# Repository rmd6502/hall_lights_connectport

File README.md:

# Hall Lights
## Directory
* TBXML
    An external library I use to parse XML
* color_picker
    An iOS front end
* hall_lights
    The Arduino sketch
* hardware
    Eagle CAD files
* lights
    Python source for the ConnectPort X2 to implement the server

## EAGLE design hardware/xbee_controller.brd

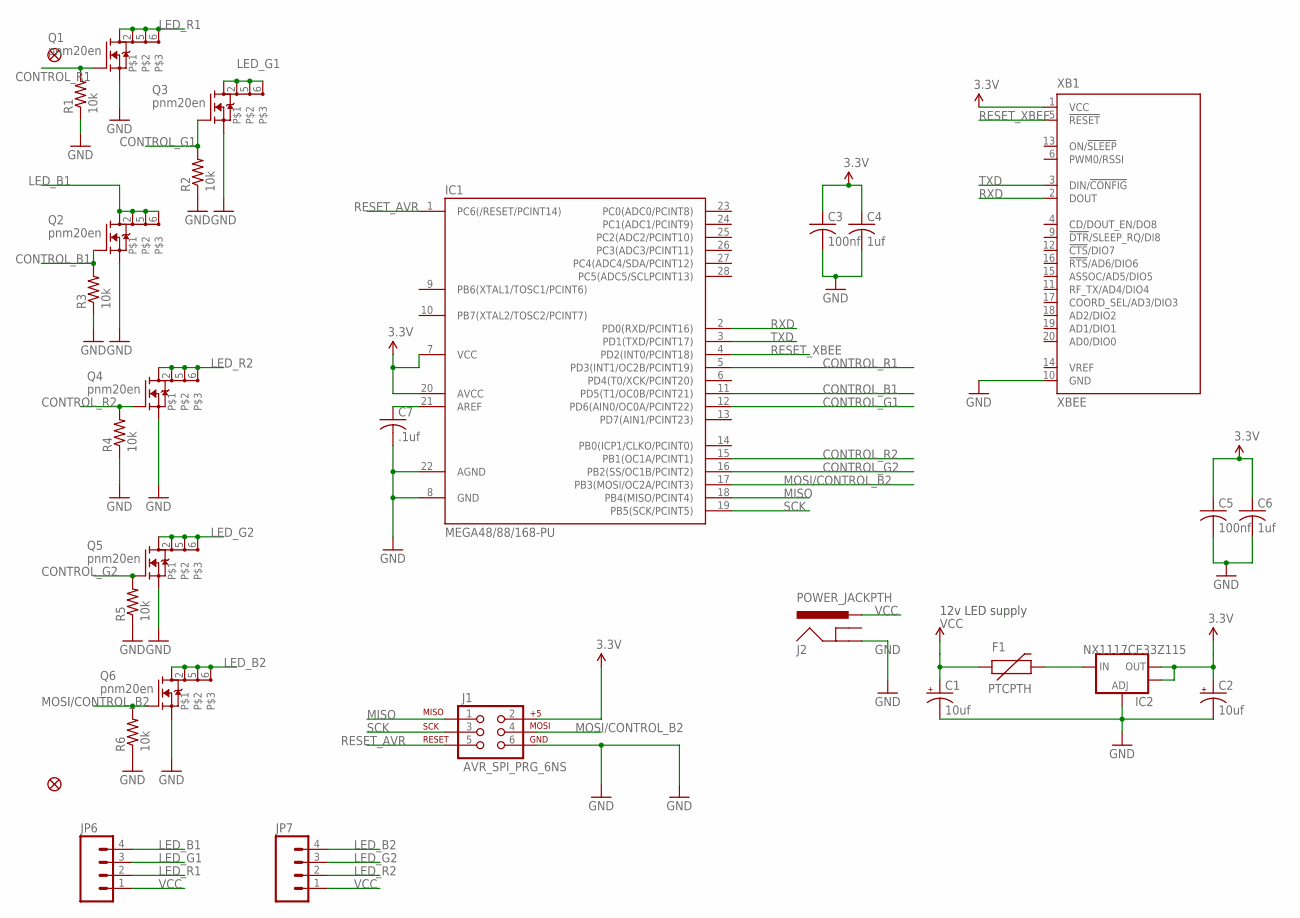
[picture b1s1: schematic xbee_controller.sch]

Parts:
C1, C2: 10uf; PANASONIC_A
C3, C5: 100nf; C0603
C4, C6: 1uf; C0603
C7: .1uf; C0603
F1: PTCPTH; PTC
IC1: MEGA48/88/168-PU; DIL28-3
IC2: NX1117CE33Z115; SOT223
J1: AVR_SPI_PRG_6NS; 2X3-NS
J2: POWER_JACKPTH; POWER_JACK_PTH
JP2, JP5: FIDUCIAL1.5X3; FIDUCIAL-1.5X3
JP6, JP7: M04SCREW; SCREWTERMINAL-3.5MM-4
Q1, Q2, Q3, Q4, Q5, Q6: pnm20en; BCR405U
R1, R2, R3, R4, R5, R6: 10k; R0603
XB1: XBEE

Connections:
3.3V: C2.+, C3.1, C4.1, C5.1, C6.1, IC1.7 (VCC), IC1.20 (AVCC), IC2.2 (OUT), IC2.4 (OUT), J1.2, XB1.1 (VCC)
CONTROL_B1: IC1.11 (PD5(T1/OC0B/PCINT21)), Q2.3 (G), R3.2
CONTROL_G1: IC1.12 (PD6(AIN0/OC0A/PCINT22)), Q3.3 (G), R2.2
CONTROL_G2: IC1.16 (PB2(SS/OC1B/PCINT2)), Q5.3 (G), R5.2
CONTROL_R1: IC1.5 (PD3(INT1/OC2B/PCINT19)), Q1.3 (G), R1.2
CONTROL_R2: IC1.15 (PB1(OC1A/PCINT1)), Q4.3 (G), R4.2
GND: C1.-, C2.-, C3.2, C4.2, C5.2, C6.2, C7.2, IC1.8 (GND), IC1.22 (AGND), IC2.1 (ADJ), J1.6, J2.GND, Q1.4 (S), Q2.4 (S), Q3.4 (S), Q4.4 (S), Q5.4 (S), Q6.4 (S), R1.1, R2.1, R3.1, R4.1, R5.1, R6.1, XB1.10 (GND)
LED_B1: JP6.4, Q2.1 (D), Q2.2, Q2.5, Q2.6
LED_B2: JP7.4, Q6.1 (D), Q6.2, Q6.5, Q6.6
LED_G1: JP6.3, Q3.1 (D), Q3.2, Q3.5, Q3.6
LED_G2: JP7.3, Q5.1 (D), Q5.2, Q5.5, Q5.6
LED_R1: JP6.2, Q1.1 (D), Q1.2, Q1.5, Q1.6
LED_R2: JP7.2, Q4.1 (D), Q4.2, Q4.5, Q4.6
MISO: IC1.18 (PB4(MISO/PCINT4)), J1.1
MOSI/CONTROL_B2: IC1.17 (PB3(MOSI/OC2A/PCINT3)), J1.4, Q6.3 (G), R6.2
unnamed: F1.P$2 (2), IC2.3 (IN)
unnamed: C7.1, IC1.21 (AREF)
RESET_AVR: IC1.1 (PC6(/RESET/PCINT14)), J1.5
RESET_XBEE: IC1.4 (PD2(INT0/PCINT18)), XB1.5 (!RESET)
RXD: IC1.2 (PD0(RXD/PCINT16)), XB1.2 (DOUT)
SCK: IC1.19 (PB5(SCK/PCINT5)), J1.3
TXD: IC1.3 (PD1(TXD/PCINT17)), XB1.3 (DIN/!CONFIG)
VCC: C1.+, F1.P$1 (1), J2.PWR, JP6.1, JP7.1

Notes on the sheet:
12v LED supply

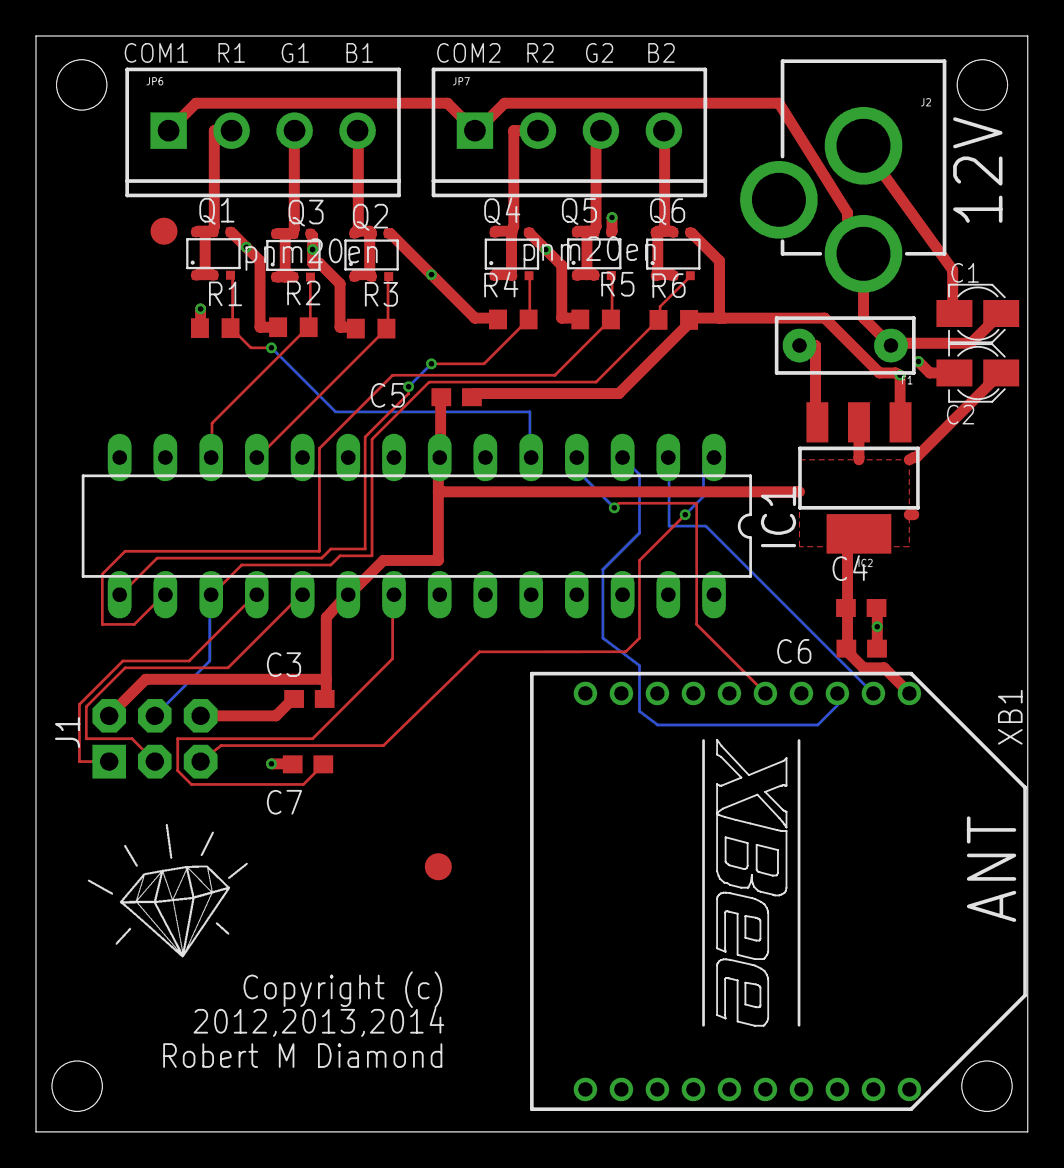
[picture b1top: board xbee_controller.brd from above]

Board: 2 copper layers, 55.1 x 60.9 mm, 29 parts (0 on the bottom side), 23 nets.

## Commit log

2012-02-26 create project with arduino sketch + digi python webserver
2012-02-26 add sort by hue, and test program
2012-02-26 oops, fix error in main lights module too
2012-02-26 handle sorting by hue, reading reply from node
2012-02-26 fix barf error
2012-02-27 speed up startup a bit
2012-02-27 add query to arduino sketch
2012-02-27 add nodelist
2012-02-27 add query
2012-02-28 add ajax update
2012-02-28 update colors more frequently, but don't mess with field the user is typing in
2012-03-01 allow initial update of page from Q result
2012-03-03 enable upload of initial lights value
2012-03-04 add eagle files now that board is shown to work
2012-03-04 change order of operations to simplify and correct logic
2012-03-04 add iphone app
2012-03-05 add awareness of server
2012-03-05 fix mistaken use of attribute for color child elements. Add spinner
2012-03-05 a few bug fixes
2012-03-05 fix fetch of lights
2012-03-05 handle non-reference-counted ios levels
2012-03-05 add customized tbxml
2012-03-09 store colors per light
2012-03-09 add refresh timer
2012-03-09 add hardware
2012-03-11 properly add tbxml
2012-03-11 add title to color picker
2012-03-11 fix array use in app
2012-03-11 add touch sensitivity
2012-03-11 allow building for ios 4.x
2012-03-11 invalidate and release timers
2012-03-11 add last heard time to query response
2012-03-11 if a node hasn't been heard in >60s color it red
2012-03-12 fix brightness range
2012-03-13 fix brightness setting, make text red when a light is inactive
2012-03-13 fix race condition in refresh
2012-03-13 calculate layout for brightness bar
2012-03-15 add lamp icon that shows current color
2012-03-17 add readme
2012-03-17 use better table cell layout
2012-03-25 refresh on app becoming active
2012-03-29 ui improvements
2012-03-30 fix all lights commands
2012-03-30 add "node=all" to the accepted values
2012-04-01 fix wire colors, enable independent control of channels
2012-04-01 clean up light discovery code a little
2012-04-06 update node name
2012-04-07 handle renaming of lights
2012-04-08 checkpoint
2012-04-08 checkpoint 2
2012-04-09 not quite working
2012-04-10 connectport discovery
2012-04-10 fix lights.py
2012-04-10 connect digi discovery
2012-04-10 more discovery
2012-04-10 more dynamic update of colors
2012-04-11 change text not value
2012-04-11 handle discovery a tiny bit better
2012-04-12 only set cport if setting is empty
2012-04-12 close socket
2012-05-22 a bit more error checking
2012-07-15 slightly smarter refreshing
2012-07-22 accept separate commands for both lights
2012-07-22 add .gitignore, tweaks for multi lights
2012-07-22 more tweaks
2012-08-01 add json support
2012-08-09 fill in node picker, 1, 2, or both - not finished yet
2012-08-16 add django project
2012-08-16 add templates
2012-08-17 add raspberry pi directory
2012-08-17 add individual light colors
2012-08-17 update template
2012-08-17 add template tags
2012-10-25 discovery bug
2013-06-24 correct pin definitions, ensure ui operations happen on main thread
2013-07-13 update to arc
2013-07-13 remove analyzer warnings
2013-07-13 set deployment target to 5.1
2013-07-21 fix copyright notices
2013-09-16 start supporting pebble
2014-05-20 add sequences
2014-05-21 add a few more messages
2014-05-21 update help
2014-05-23 save speed
2014-05-23 handle bad seq
2014-05-24 possibly handle second controller on sequences
2014-05-26 start implementing server
2014-05-26 add set
2014-05-27 remove debugging
2014-05-27 add color parse
2014-05-27 colors
2014-05-27 template
2014-05-27 just handle 1 and 2 and we're ready
2014-05-28 two lights
2014-05-28 all on/off
2014-05-29 wsgi
2014-05-30 fix html and case
2014-05-30 sort
2014-05-31 sequences
2014-05-31 more seq
2014-05-31 python and port
2014-05-31 layout-ish
2014-05-31 play and stop
2014-05-31 start saving seqs
2014-05-31 config
2014-06-01 comments
2014-06-02 get it to build
2014-06-13 two colors
2014-06-13 update pin numbers
2014-06-15 help
2014-06-16 add cr
2014-08-11 add better example server files
2014-08-12 update jscolor, fix persistent picker
2014-08-16 update colors
2014-08-16 fix color updates
2014-12-13 start watch app
2015-04-12 remove tbxml
2015-04-12 make it build again
2015-04-26 add watchapp
2015-04-27 set colors
2015-04-29 it almost works
2015-04-29 comment out printf
2015-05-02 add icon, fix bugs
2015-05-02 jump through flaming hoops
2015-05-02 add icons
2015-05-03 color list
2015-05-03 shrink the color list to make things reasonable
2015-05-03 a little bit more interactivity
2015-05-03 update version
2015-05-03 add outline
2015-05-03 fix label
2015-05-06 fix color selection
2015-05-19 update to uialertcontroller
2015-05-19 dismiss alert on enter background
2015-05-22 ui updates
2015-10-11 remove secret key
